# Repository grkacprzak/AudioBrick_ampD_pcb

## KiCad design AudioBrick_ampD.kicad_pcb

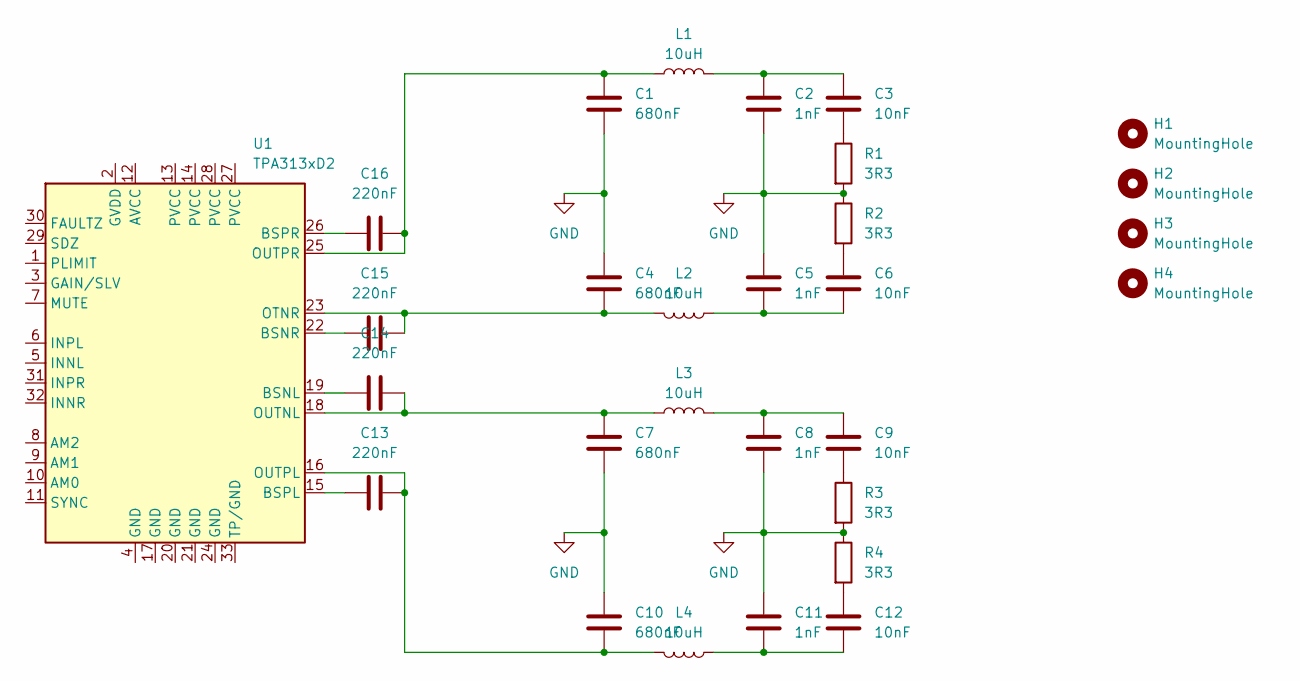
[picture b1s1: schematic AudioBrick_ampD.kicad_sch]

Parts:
C1, C4, C7, C10: 680nF; C_0603_1608Metric
C2, C5, C8, C11: 1nF; C_0603_1608Metric
C3, C6, C9, C12: 10nF; C_0603_1608Metric
C13, C14, C15, C16: 220nF; C_0603_1608Metric
H1, H2, H3, H4: MountingHole; MountingHole_3.2mm_M3
L1, L2, L3, L4: 10uH; L_10.4x10.4_H4.8
R1, R2, R3, R4: 3R3; R_0603_1608Metric
U1: TPA313xD2; VQFN-32-1EP_5x5mm_P0.5mm_EP3.5x3.5mm_ThermalVias

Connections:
GND: C1.2, C2.2, C4.1, C5.1, C7.2, C8.2, C10.1, C11.1, R1.2, R2.1, R3.2, R4.1
unnamed: C2.1, C3.1, L1.2
unnamed: C3.2, R1.1
unnamed: C5.2, C6.2, L2.1
unnamed: C6.1, R2.2
unnamed: C8.1, C9.1, L3.1
unnamed: C9.2, R3.1
unnamed: C11.2, C12.2, L4.2
unnamed: C12.1, R4.2
unnamed: C14.1, U1.19 (BSNL)
unnamed: C15.1, U1.22 (BSNR)
unnamed: C13.1, U1.15 (BSPL)
unnamed: C16.1, U1.26 (BSPR)
unnamed: C4.2, C15.2, L2.2, U1.23 (OTNR)
unnamed: C7.1, C14.2, L3.2, U1.18 (OUTNL)
unnamed: C10.2, C13.2, L4.1, U1.16 (OUTPL)
unnamed: C1.1, C16.2, L1.1, U1.25 (OUTPR)

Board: 2 copper layers, 29 parts (0 on the bottom side), 17 nets, no tracks yet.

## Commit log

2024-10-07 add files
2024-10-10 output LC filter
